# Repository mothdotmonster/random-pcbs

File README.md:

These are random PCB designs I've made. You can do whatever you want with them.

They have probably not been tested and come with no guarantees. Make them at your own risk.

These works are licensed under a
[Creative Commons Attribution-ShareAlike 4.0 International License][cc-by-sa].

[![CC BY-SA 4.0][cc-by-sa-image]][cc-by-sa]

[cc-by-sa]: http://creativecommons.org/licenses/by-sa/4.0/
[cc-by-sa-image]: https://licensebuttons.net/l/by-sa/4.0/88x31.png

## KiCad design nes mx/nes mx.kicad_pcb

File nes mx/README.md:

This board is for an NES controller that would use Cherry MX keyboard buttons. I will probably get this made and design an enclosure for it some day.

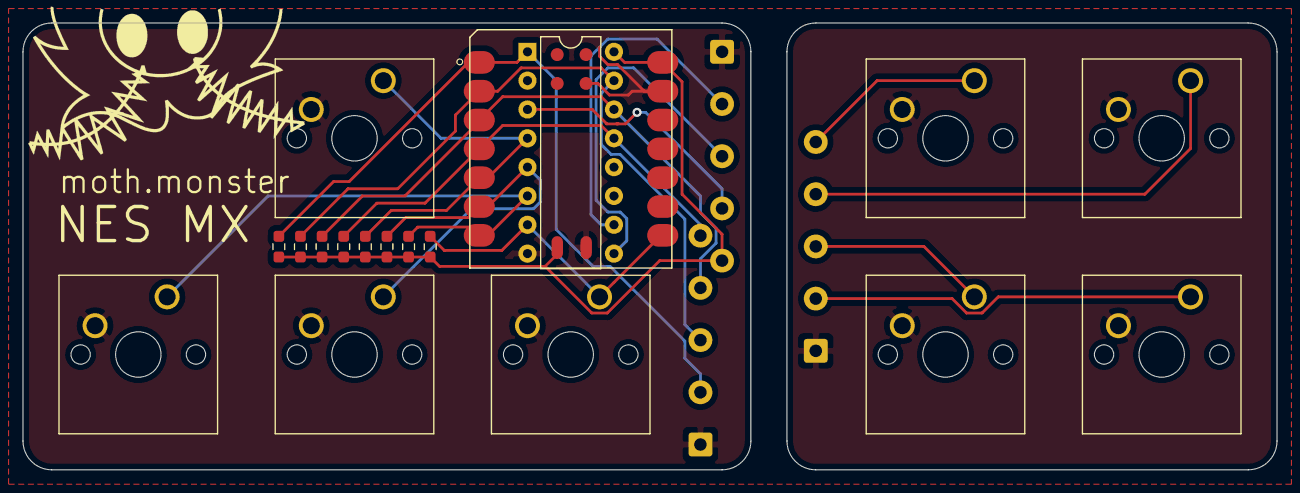
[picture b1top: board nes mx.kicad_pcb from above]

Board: 2 copper layers, 110.5 x 39.4 mm, 20 parts (0 on the bottom side), 13 nets.

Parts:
J1: Conn_01x05; SolderWire-0.5sqmm_1x05_P4.6mm_D0.9mm_OD2.1mm
R1, R2, R3, R4, R5, R6, R7, R8: R_US; R_0603_1608Metric_Pad0.98x0.95mm_HandSolder
Ref**: Val**; mothfacemedium
SW1: RIGHT; SW_Cherry_MX_1.00u_PCB
SW2: DOWN; SW_Cherry_MX_1.00u_PCB
SW3: START; SW_Cherry_MX_1.00u_PCB
SW4: B; SW_Cherry_MX_1.00u_PCB
SW5: LEFT; SW_Cherry_MX_1.00u_PCB
SW6: UP; SW_Cherry_MX_1.00u_PCB
SW7: SELECT; SW_Cherry_MX_1.00u_PCB
SW8: A; SW_Cherry_MX_1.00u_PCB
U1: 4021; DIP-16_W7.62mm
U2: SeeeduinoXIAO; Seeeduino XIAO-MOUDLE14P-2.54-21X17.8MM

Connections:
+5V: J1.5, R1.2, R2.2, R3.2, R4.2, R5.2, R6.2, R7.2, R8.2, U1.16, U2.14, U2.15
C: J1.2, U1.10
D: J1.4, U1.3
GND: J1.1, SW1.2, SW2.2, SW3.2, SW4.2, SW5.2, SW6.2, SW7.2, SW8.2, U1.8, U2.13, U2.16, U2.20
L: J1.3, U1.9
unnamed: R1.1, SW8.1, U1.1, U2.1
unnamed: R2.1, SW4.1, U1.15, U2.2
unnamed: R3.1, SW7.1, U1.14, U2.3
unnamed: R4.1, SW3.1, U1.13, U2.4
unnamed: R5.1, SW6.1, U1.4, U2.5
unnamed: R6.1, SW2.1, U1.5, U2.6
unnamed: R7.1, SW5.1, U1.6, U2.7
unnamed: R8.1, SW1.1, U1.7, U2.8

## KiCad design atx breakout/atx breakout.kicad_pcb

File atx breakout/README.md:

An ATX power supply breakout board.

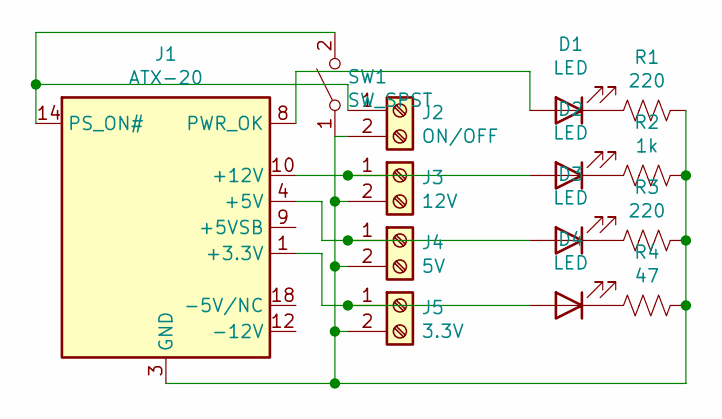
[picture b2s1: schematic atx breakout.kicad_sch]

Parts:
D1, D2, D3, D4: LED; LED_D5.0mm
J1: ATX-20; Molex_Mini-Fit_Jr_5566-20A2_2x10_P4.20mm_Vertical
J2: ON/OFF; TerminalBlock_Altech_AK300-2_P5.00mm
J3: 12V; TerminalBlock_Altech_AK300-2_P5.00mm
J4: 5V; TerminalBlock_Altech_AK300-2_P5.00mm
J5: 3.3V; TerminalBlock_Altech_AK300-2_P5.00mm
R1, R3: 220; R_Axial_DIN0207_L6.3mm_D2.5mm_P10.16mm_Horizontal
R2: 1k; R_Axial_DIN0207_L6.3mm_D2.5mm_P10.16mm_Horizontal
R4: 47; R_Axial_DIN0207_L6.3mm_D2.5mm_P10.16mm_Horizontal
SW1: SW_SPST; PinHeader_1x03_P2.54mm_Vertical

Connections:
unnamed: D1.1 (K), R1.2
unnamed: D1.2 (A), J1.8 (PWR_OK)
unnamed: D2.1 (K), R2.2
unnamed: D2.2 (A), J1.10 (+12V), J3.1
unnamed: D3.1 (K), R3.2
unnamed: D3.2 (A), J1.4 (+5V), J1.6 (+5V), J1.19 (+5V), J1.20 (+5V), J4.1
unnamed: D4.1 (K), R4.2
unnamed: D4.2 (A), J1.1 (+3.3V), J1.2 (+3.3V), J1.11 (+3.3V), J5.1
unnamed: J1.3 (GND), J1.5 (GND), J1.7 (GND), J1.13 (GND), J1.15 (GND), J1.16 (GND), J1.17 (GND), J2.2, J3.2, J4.2, J5.2, R1.1, R2.1, R3.1, R4.1, SW1.1 (A)
unnamed: J1.14 (PS_ON#), J2.1, SW1.2 (B)

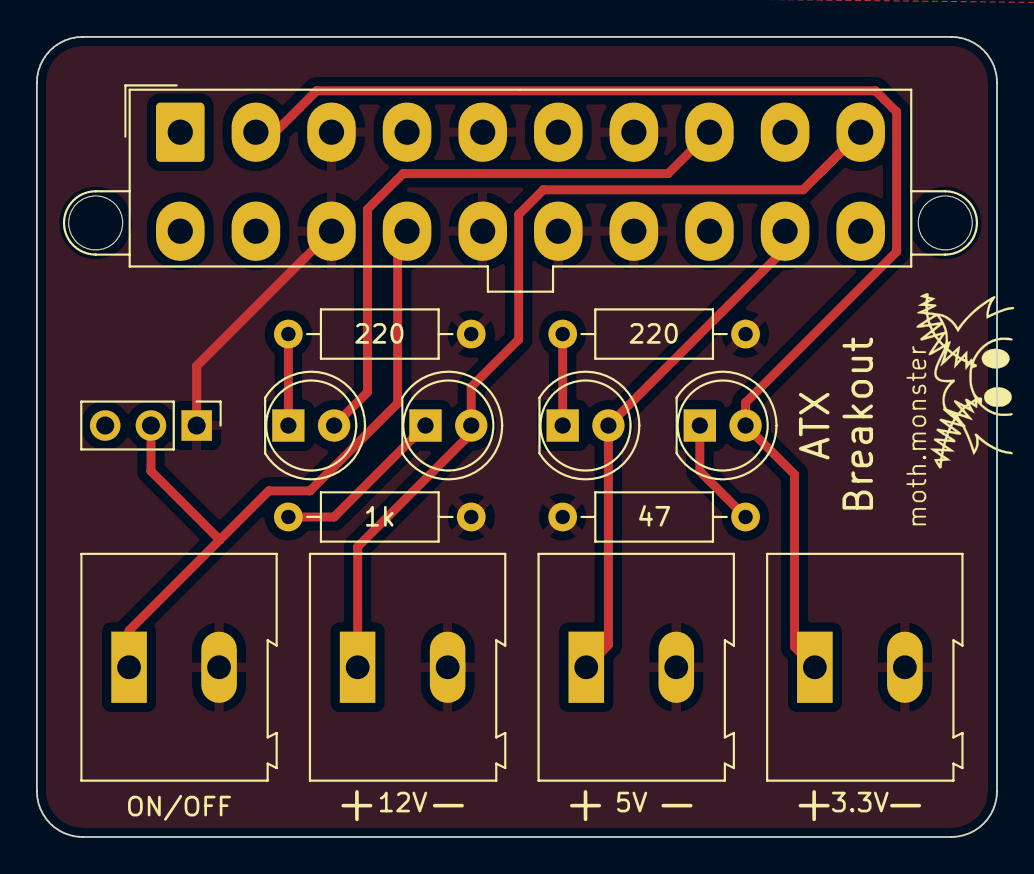
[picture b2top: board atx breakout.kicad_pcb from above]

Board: 2 copper layers, 53.3 x 44.5 mm, 15 parts (0 on the bottom side), 10 nets.

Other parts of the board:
Ref**: Val**; mothfacefixed

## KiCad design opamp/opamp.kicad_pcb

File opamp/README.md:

This is a recreation of the classic LM741 op-amp using standard THT components.

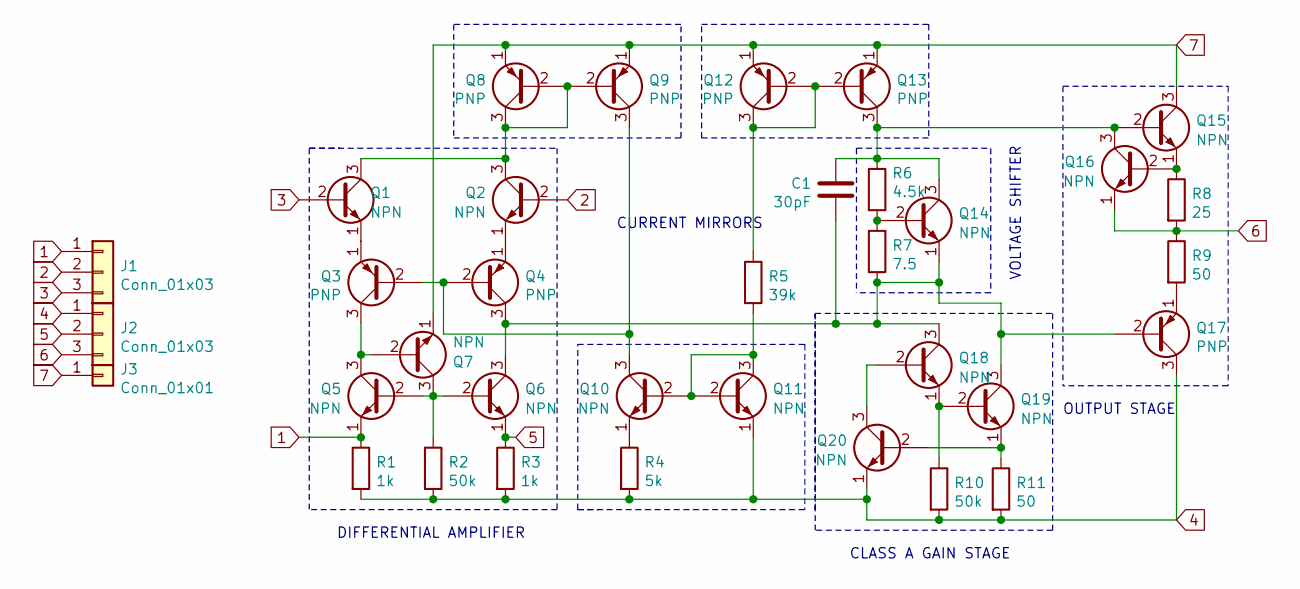
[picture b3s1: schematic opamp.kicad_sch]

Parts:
C1: 30pF; C_Disc_D3.0mm_W2.0mm_P2.50mm
J1, J2: Conn_01x03; PinSocket_1x03_P2.54mm_Vertical
J3: Conn_01x01; PinSocket_1x01_P2.54mm_Vertical
Q1, Q2, Q5, Q6, Q7, Q10, Q11, Q14, Q15, Q16, Q18, Q19, Q20: NPN; TO-92
Q3, Q4, Q8, Q9, Q12, Q13, Q17: PNP; TO-92
R1, R3: 1k; R_Axial_DIN0207_L6.3mm_D2.5mm_P7.62mm_Horizontal
R2, R10: 50k; R_Axial_DIN0207_L6.3mm_D2.5mm_P7.62mm_Horizontal
R4: 5k; R_Axial_DIN0207_L6.3mm_D2.5mm_P7.62mm_Horizontal
R5: 39k; R_Axial_DIN0207_L6.3mm_D2.5mm_P7.62mm_Horizontal
R6: 4.5k; R_Axial_DIN0207_L6.3mm_D2.5mm_P7.62mm_Horizontal
R7: 7.5; R_Axial_DIN0207_L6.3mm_D2.5mm_P7.62mm_Horizontal
R8: 25; R_Axial_DIN0207_L6.3mm_D2.5mm_P7.62mm_Horizontal
R9, R11: 50; R_Axial_DIN0207_L6.3mm_D2.5mm_P7.62mm_Horizontal

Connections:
1: J1.1, Q5.1 (E), R1.1
2: J1.2, Q2.2 (B)
3: J1.3, Q1.2 (B)
4: J2.1, Q11.1 (E), Q17.3 (C), Q20.1 (E), R1.2, R2.2, R3.2, R4.2, R10.2, R11.2
5: J2.2, Q6.1 (E), R3.1
6: J2.3, Q16.1 (E), R8.2, R9.1
7: J3.1, Q7.1 (E), Q8.1 (E), Q9.1 (E), Q12.1 (E), Q13.1 (E), Q15.3 (C)
unnamed: C1.2, Q13.3 (C), Q14.3 (C), Q15.2 (B), Q16.3 (C), R6.1
unnamed: Q1.3 (C), Q2.3 (C), Q8.2 (B), Q8.3 (C), Q9.2 (B)
unnamed: Q1.1 (E), Q3.1 (E)
unnamed: Q2.1 (E), Q4.1 (E)
unnamed: Q3.2 (B), Q4.2 (B), Q9.3 (C), Q10.3 (C)
unnamed: Q3.3 (C), Q5.3 (C), Q7.2 (B)
unnamed: Q5.2 (B), Q6.2 (B), Q7.3 (C), R2.1
unnamed: C1.1, Q4.3 (C), Q6.3 (C), Q14.1 (E), Q17.2 (B), Q18.3 (C), Q19.3 (C), R7.2
unnamed: Q10.1 (E), R4.1
unnamed: Q10.2 (B), Q11.2 (B), Q11.3 (C), R5.2
unnamed: Q14.2 (B), R6.2, R7.1
unnamed: Q15.1 (E), Q16.2 (B), R8.1
unnamed: Q18.1 (E), Q19.2 (B), R10.1
unnamed: Q18.2 (B), Q20.3 (C)
unnamed: Q19.1 (E), Q20.2 (B), R11.1
unnamed: Q12.2 (B), Q12.3 (C), Q13.2 (B), R5.1
unnamed: Q17.1 (E), R9.2

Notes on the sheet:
DIFFERENTIAL AMPLIFIER
CURRENT MIRRORS
CLASS A GAIN STAGE
VOLTAGE SHIFTER
OUTPUT STAGE

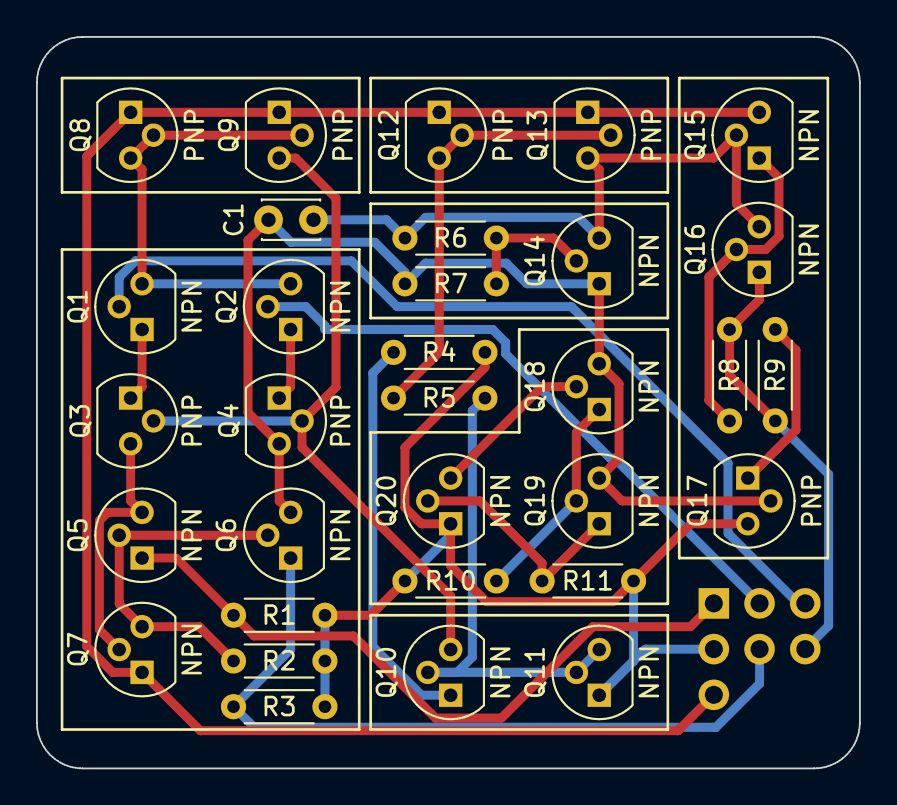
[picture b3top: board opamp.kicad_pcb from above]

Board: 2 copper layers, 45.7 x 40.6 mm, 36 parts (1 on the bottom side), 24 nets.

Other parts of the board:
Ref**: Val**; mothfacemedium

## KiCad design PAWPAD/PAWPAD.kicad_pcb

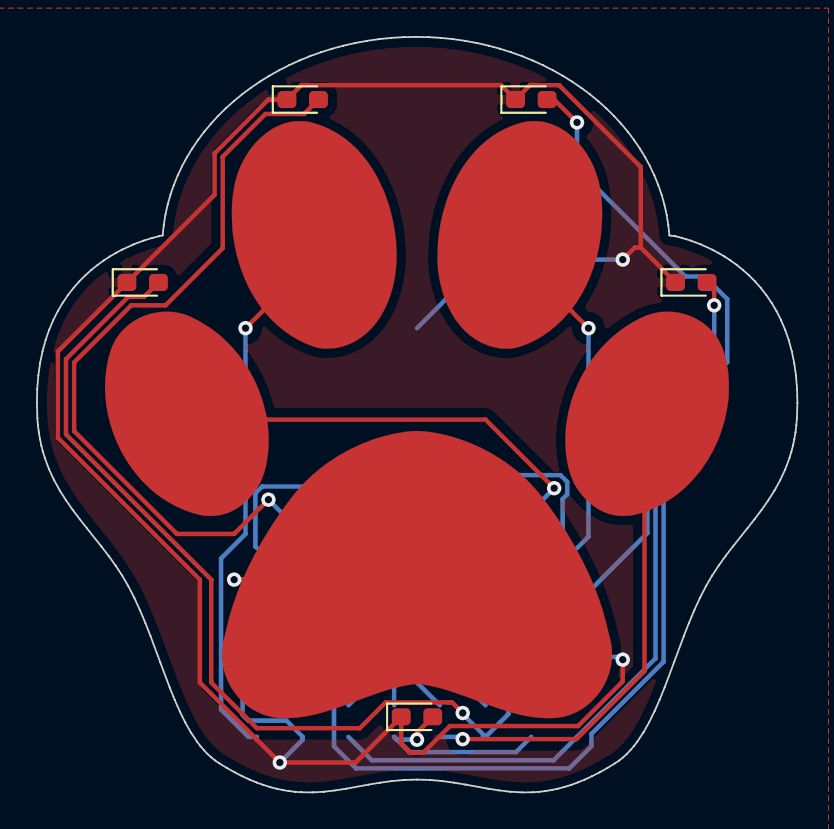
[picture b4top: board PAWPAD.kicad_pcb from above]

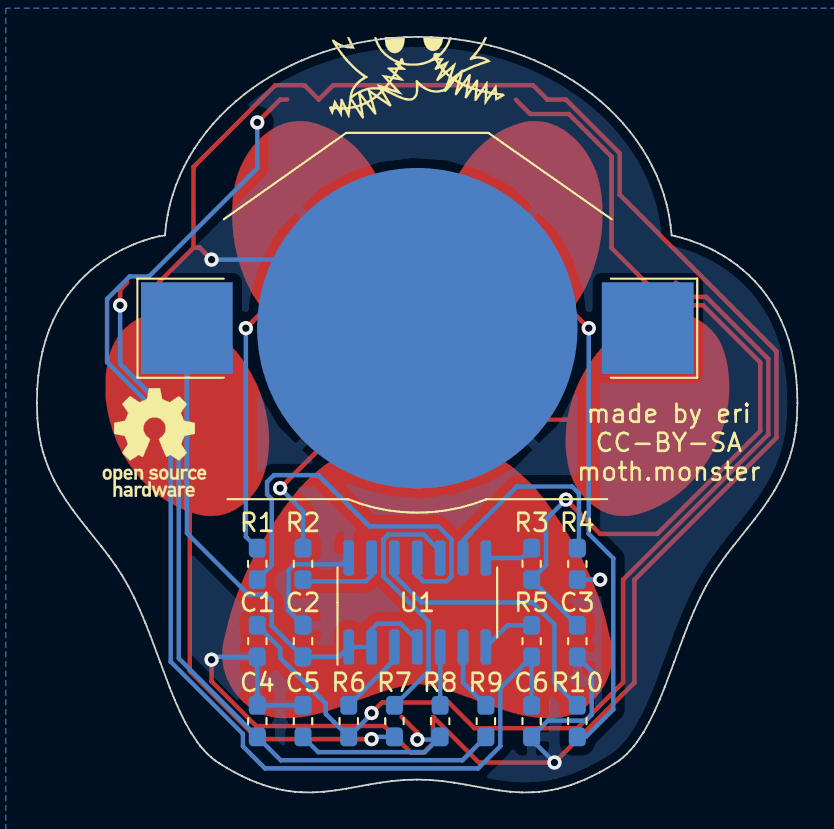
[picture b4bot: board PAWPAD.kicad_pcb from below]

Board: 2 copper layers, 42.3 x 42.0 mm, 30 parts (19 on the bottom side), 22 nets.

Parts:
BT1: Battery_Cell; BatteryHolder_Keystone_3002_1x2032
C1, C3, C4, C5: C; C_0603_1608Metric_Pad1.05x0.95mm_HandSolder
C2: 0.1µf; C_0603_1608Metric_Pad1.05x0.95mm_HandSolder
C6: 4.7k; R_0603_1608Metric_Pad1.05x0.95mm_HandSolder
D1, D2, D3, D4, D5: LED; LED_0603_1608Metric_Pad1.05x0.95mm_HandSolder
J1, J2, J3, J4, J5: Conn_01x01; TestPoint_Pad_4.0x4.0mm
R1, R2, R3, R4, R5, R6, R7, R8, R9: 4.7k; R_0603_1608Metric_Pad1.05x0.95mm_HandSolder
R10: C; C_0603_1608Metric_Pad1.05x0.95mm_HandSolder
Ref**: Val**; mothface
Ref**#2: Val**; pawpad
U1: AT42QT1070-S; SOIC-14_3.9x8.7mm_P1.27mm

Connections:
GND: BT1.2, C1.1, C2.1, C3.2, C4.1, C5.1, D1.1, D2.1, D3.1, D4.1, D5.1, R10.2, U1.14
unnamed: C5.2, D5.2, R8.2
unnamed: C1.2, D1.2, R6.2
unnamed: C4.2, D4.2, R9.2
unnamed: D3.2, R5.1, R10.1
unnamed: C3.1, D2.2, R3.1
unnamed: J1.1, R2.1
unnamed: C6.1, J2.1
unnamed: J3.1, R1.1
unnamed: J4.1, R7.1
unnamed: J5.1, R4.1
unnamed: R6.1, U1.3
unnamed: R9.1, U1.6
unnamed: R8.1, U1.5
unnamed: R2.2, U1.13
unnamed: C6.2, U1.12
unnamed: R1.2, U1.11
unnamed: R7.2, U1.10
unnamed: R4.2, U1.9
unnamed: R3.2, U1.8
unnamed: R5.2, U1.7
VDD: BT1.1, C2.2, U1.1, U1.2, U1.4

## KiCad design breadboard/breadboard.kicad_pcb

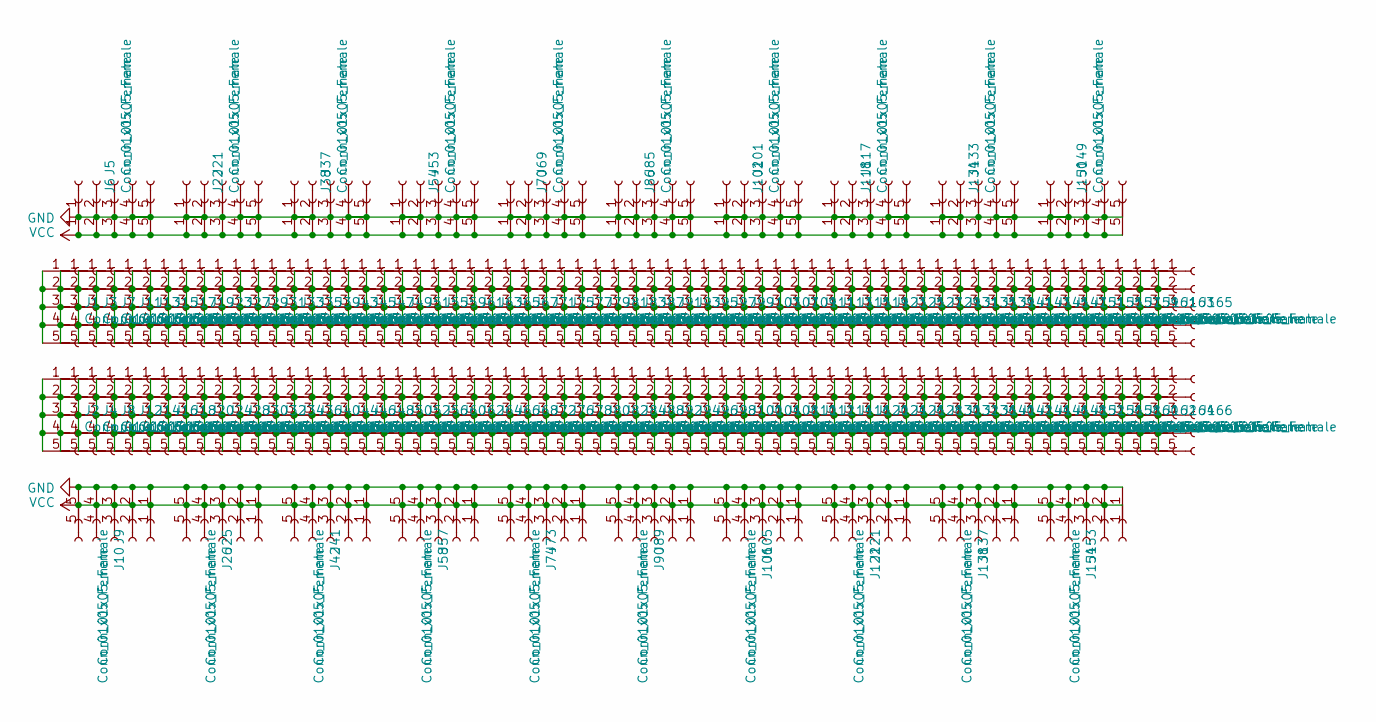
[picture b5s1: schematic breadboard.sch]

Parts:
J1, J2, J3, J4, J5, J6, J7, J8, J9, J10, J11, J12, J13, J14, J15, J16, J17, J18, J19, J20, J21, J22, J23, J24, J25, J26, J27, J28, J29, J30, J31, J32, J33, J34, J35, J36, J37, J38, J39, J40, J41, J42, J43, J44, J45, J46, J47, J48, J49, J50, J51, J52, J53, J54, J55, J56, J57, J58, J59, J60, J61, J62, J63, J64, J65, J66, J67, J68, J69, J70, J71, J72, J73, J74, J75, J76, J77, J78, J79, J80, J81, J82, J83, J84, J85, J86, J87, J88, J89, J90, J91, J92, J93, J94, J95, J96, J97, J98, J99, J100, J101, J102, J103, J104, J105, J106, J107, J108, J109, J110, J111, J112, J113, J114, J115, J116, J117, J118, J119, J120, J121, J122, J123, J124, J125, J126, J127, J128, J129, J130, J131, J132, J133, J134, J135, J136, J137, J138, J139, J140, J141, J142, J143, J144, J145, J146, J147, J148, J149, J150, J151, J152, J153, J154, J155, J156, J157, J158, J159, J160, J161, J162, J163, J164, J165, J166: Conn_01x05_Female; PinSocket_1x05_P2.54mm_Vertical

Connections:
GND: J5.1, J5.2, J5.3, J5.4, J5.5, J9.1, J9.2, J9.3, J9.4, J9.5, J21.1, J21.2, J21.3, J21.4, J21.5, J25.1, J25.2, J25.3, J25.4, J25.5, J37.1, J37.2, J37.3, J37.4, J37.5, J41.1, J41.2, J41.3, J41.4, J41.5, J53.1, J53.2, J53.3, J53.4, J53.5, J57.1, J57.2, J57.3, J57.4, J57.5, J69.1, J69.2, J69.3, J69.4, J69.5, J73.1, J73.2, J73.3, J73.4, J73.5, J85.1, J85.2, J85.3, J85.4, J85.5, J89.1, J89.2, J89.3, J89.4, J89.5, J101.1, J101.2, J101.3, J101.4, J101.5, J105.1, J105.2, J105.3, J105.4, J105.5, J117.1, J117.2, J117.3, J117.4, J117.5, J121.1, J121.2, J121.3, J121.4, J121.5, J133.1, J133.2, J133.3, J133.4, J133.5, J137.1, J137.2, J137.3, J137.4, J137.5, J149.1, J149.2, J149.3, J149.4, J149.5, J153.1, J153.2, J153.3, J153.4, J153.5
unnamed: J1.1, J1.2, J1.3, J1.4, J1.5
unnamed: J2.1, J2.2, J2.3, J2.4, J2.5
unnamed: J3.1, J3.2, J3.3, J3.4, J3.5
unnamed: J4.1, J4.2, J4.3, J4.4, J4.5
unnamed: J7.1, J7.2, J7.3, J7.4, J7.5
unnamed: J8.1, J8.2, J8.3, J8.4, J8.5
unnamed: J11.1, J11.2, J11.3, J11.4, J11.5
unnamed: J12.1, J12.2, J12.3, J12.4, J12.5
unnamed: J13.1, J13.2, J13.3, J13.4, J13.5
unnamed: J14.1, J14.2, J14.3, J14.4, J14.5
unnamed: J15.1, J15.2, J15.3, J15.4, J15.5
unnamed: J16.1, J16.2, J16.3, J16.4, J16.5
unnamed: J17.1, J17.2, J17.3, J17.4, J17.5
unnamed: J18.1, J18.2, J18.3, J18.4, J18.5
unnamed: J19.1, J19.2, J19.3, J19.4, J19.5
unnamed: J20.1, J20.2, J20.3, J20.4, J20.5
unnamed: J23.1, J23.2, J23.3, J23.4, J23.5
unnamed: J24.1, J24.2, J24.3, J24.4, J24.5
unnamed: J27.1, J27.2, J27.3, J27.4, J27.5
unnamed: J28.1, J28.2, J28.3, J28.4, J28.5
unnamed: J29.1, J29.2, J29.3, J29.4, J29.5
unnamed: J30.1, J30.2, J30.3, J30.4, J30.5
unnamed: J31.1, J31.2, J31.3, J31.4, J31.5
unnamed: J32.1, J32.2, J32.3, J32.4, J32.5
unnamed: J33.1, J33.2, J33.3, J33.4, J33.5
unnamed: J34.1, J34.2, J34.3, J34.4, J34.5
unnamed: J35.1, J35.2, J35.3, J35.4, J35.5
unnamed: J36.1, J36.2, J36.3, J36.4, J36.5
unnamed: J39.1, J39.2, J39.3, J39.4, J39.5
unnamed: J40.1, J40.2, J40.3, J40.4, J40.5
unnamed: J43.1, J43.2, J43.3, J43.4, J43.5
unnamed: J44.1, J44.2, J44.3, J44.4, J44.5
unnamed: J45.1, J45.2, J45.3, J45.4, J45.5
unnamed: J46.1, J46.2, J46.3, J46.4, J46.5
unnamed: J47.1, J47.2, J47.3, J47.4, J47.5
unnamed: J48.1, J48.2, J48.3, J48.4, J48.5
unnamed: J49.1, J49.2, J49.3, J49.4, J49.5
unnamed: J50.1, J50.2, J50.3, J50.4, J50.5
unnamed: J51.1, J51.2, J51.3, J51.4, J51.5
unnamed: J52.1, J52.2, J52.3, J52.4, J52.5
unnamed: J55.1, J55.2, J55.3, J55.4, J55.5
unnamed: J56.1, J56.2, J56.3, J56.4, J56.5
unnamed: J59.1, J59.2, J59.3, J59.4, J59.5
unnamed: J60.1, J60.2, J60.3, J60.4, J60.5
unnamed: J61.1, J61.2, J61.3, J61.4, J61.5
unnamed: J62.1, J62.2, J62.3, J62.4, J62.5
unnamed: J63.1, J63.2, J63.3, J63.4, J63.5
unnamed: J64.1, J64.2, J64.3, J64.4, J64.5
unnamed: J65.1, J65.2, J65.3, J65.4, J65.5
unnamed: J66.1, J66.2, J66.3, J66.4, J66.5
unnamed: J67.1, J67.2, J67.3, J67.4, J67.5
unnamed: J68.1, J68.2, J68.3, J68.4, J68.5
unnamed: J71.1, J71.2, J71.3, J71.4, J71.5
unnamed: J72.1, J72.2, J72.3, J72.4, J72.5
unnamed: J75.1, J75.2, J75.3, J75.4, J75.5
unnamed: J76.1, J76.2, J76.3, J76.4, J76.5
unnamed: J77.1, J77.2, J77.3, J77.4, J77.5
unnamed: J78.1, J78.2, J78.3, J78.4, J78.5
unnamed: J79.1, J79.2, J79.3, J79.4, J79.5
unnamed: J80.1, J80.2, J80.3, J80.4, J80.5
unnamed: J81.1, J81.2, J81.3, J81.4, J81.5
unnamed: J82.1, J82.2, J82.3, J82.4, J82.5
unnamed: J83.1, J83.2, J83.3, J83.4, J83.5
unnamed: J84.1, J84.2, J84.3, J84.4, J84.5
unnamed: J87.1, J87.2, J87.3, J87.4, J87.5
unnamed: J88.1, J88.2, J88.3, J88.4, J88.5
unnamed: J91.1, J91.2, J91.3, J91.4, J91.5
unnamed: J92.1, J92.2, J92.3, J92.4, J92.5
unnamed: J93.1, J93.2, J93.3, J93.4, J93.5
unnamed: J94.1, J94.2, J94.3, J94.4, J94.5
unnamed: J95.1, J95.2, J95.3, J95.4, J95.5
unnamed: J96.1, J96.2, J96.3, J96.4, J96.5
unnamed: J97.1, J97.2, J97.3, J97.4, J97.5
unnamed: J98.1, J98.2, J98.3, J98.4, J98.5
unnamed: J100.1, J100.2, J100.3, J100.4, J100.5
unnamed: J103.1, J103.2, J103.3, J103.4, J103.5
unnamed: J104.1, J104.2, J104.3, J104.4, J104.5
unnamed: J107.1, J107.2, J107.3, J107.4, J107.5
unnamed: J108.1, J108.2, J108.3, J108.4, J108.5
unnamed: J109.1, J109.2, J109.3, J109.4, J109.5
unnamed: J110.1, J110.2, J110.3, J110.4, J110.5
unnamed: J111.1, J111.2, J111.3, J111.4, J111.5
unnamed: J112.1, J112.2, J112.3, J112.4, J112.5
unnamed: J113.1, J113.2, J113.3, J113.4, J113.5
unnamed: J114.1, J114.2, J114.3, J114.4, J114.5
unnamed: J115.1, J115.2, J115.3, J115.4, J115.5
unnamed: J116.1, J116.2, J116.3, J116.4, J116.5
unnamed: J119.1, J119.2, J119.3, J119.4, J119.5
unnamed: J120.1, J120.2, J120.3, J120.4, J120.5
unnamed: J123.1, J123.2, J123.3, J123.4, J123.5
unnamed: J124.1, J124.2, J124.3, J124.4, J124.5
unnamed: J125.1, J125.2, J125.3, J125.4, J125.5
unnamed: J126.1, J126.2, J126.3, J126.4, J126.5
unnamed: J127.1, J127.2, J127.3, J127.4, J127.5
unnamed: J128.1, J128.2, J128.3, J128.4, J128.5
unnamed: J129.1, J129.2, J129.3, J129.4, J129.5
unnamed: J130.1, J130.2, J130.3, J130.4, J130.5
unnamed: J131.1, J131.2, J131.3, J131.4, J131.5
unnamed: J132.1, J132.2, J132.3, J132.4, J132.5
unnamed: J135.1, J135.2, J135.3, J135.4, J135.5
unnamed: J136.1, J136.2, J136.3, J136.4, J136.5
unnamed: J139.1, J139.2, J139.3, J139.4, J139.5
unnamed: J140.1, J140.2, J140.3, J140.4, J140.5
unnamed: J141.1, J141.2, J141.3, J141.4, J141.5
unnamed: J142.1, J142.2, J142.3, J142.4, J142.5
unnamed: J143.1, J143.2, J143.3, J143.4, J143.5
unnamed: J144.1, J144.2, J144.3, J144.4, J144.5
unnamed: J145.1, J145.2, J145.3, J145.4, J145.5
unnamed: J146.1, J146.2, J146.3, J146.4, J146.5
unnamed: J147.1, J147.2, J147.3, J147.4, J147.5
unnamed: J148.1, J148.2, J148.3, J148.4, J148.5
unnamed: J151.1, J151.2, J151.3, J151.4, J151.5
unnamed: J152.1, J152.2, J152.3, J152.4, J152.5
unnamed: J155.1, J155.2, J155.3, J155.4, J155.5
unnamed: J156.1, J156.2, J156.3, J156.4, J156.5
unnamed: J157.1, J157.2, J157.3, J157.4, J157.5
unnamed: J158.1, J158.2, J158.3, J158.4, J158.5
unnamed: J159.1, J159.2, J159.3, J159.4, J159.5
unnamed: J160.1, J160.2, J160.3, J160.4, J160.5
unnamed: J161.1, J161.2, J161.3, J161.4, J161.5
unnamed: J162.1, J162.2, J162.3, J162.4, J162.5
unnamed: J163.1, J163.2, J163.3, J163.4, J163.5
unnamed: J164.1, J164.2, J164.3, J164.4, J164.5
unnamed: J165.1, J165.2, J165.3, J165.4, J165.5
unnamed: J166.1, J166.2, J166.3, J166.4, J166.5
VCC: J6.1, J6.2, J6.3, J6.4, J6.5, J10.1, J10.2, J10.3, J10.4, J10.5, J22.1, J22.2, J22.3, J22.4, J22.5, J26.1, J26.2, J26.3, J26.4, J26.5, J38.1, J38.2, J38.3, J38.4, J38.5, J42.1, J42.2, J42.3, J42.4, J42.5, J54.1, J54.2, J54.3, J54.4, J54.5, J58.1, J58.2, J58.3, J58.4, J58.5, J70.1, J70.2, J70.3, J70.4, J70.5, J74.1, J74.2, J74.3, J74.4, J74.5, J86.1, J86.2, J86.3, J86.4, J86.5, J90.1, J90.2, J90.3, J90.4, J90.5, J102.1, J102.2, J102.3, J102.4, J102.5, J106.1, J106.2, J106.3, J106.4, J106.5, J118.1, J118.2, J118.3, J118.4, J118.5, J122.1, J122.2, J122.3, J122.4, J122.5, J134.1, J134.2, J134.3, J134.4, J134.5, J138.1, J138.2, J138.3, J138.4, J138.5, J150.1, J150.2, J150.3, J150.4, J150.5, J154.1, J154.2, J154.3, J154.4, J154.5

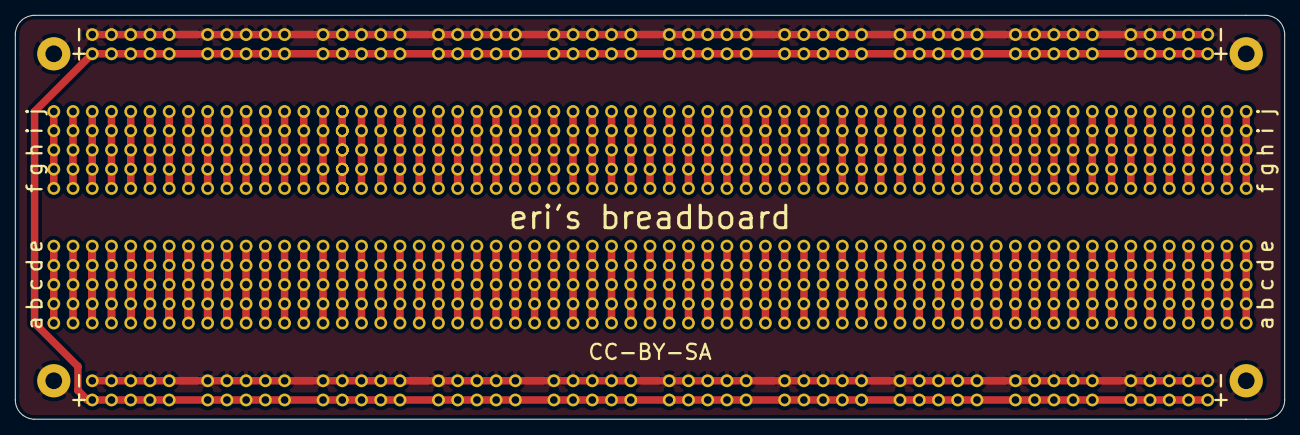
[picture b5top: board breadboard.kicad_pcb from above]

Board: 2 copper layers, 167.6 x 53.3 mm, 167 parts (0 on the bottom side), 128 nets.

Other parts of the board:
J99#2: Conn_01x05_Female; breadboardpins

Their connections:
unnamed: J99#2.1, J99#2.2, J99#2.3, J99#2.4, J99#2.5

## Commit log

2021-04-17 update silkscreen
2021-04-21 new pcb who up
2021-04-21 add picture
2021-04-21 fix switch
